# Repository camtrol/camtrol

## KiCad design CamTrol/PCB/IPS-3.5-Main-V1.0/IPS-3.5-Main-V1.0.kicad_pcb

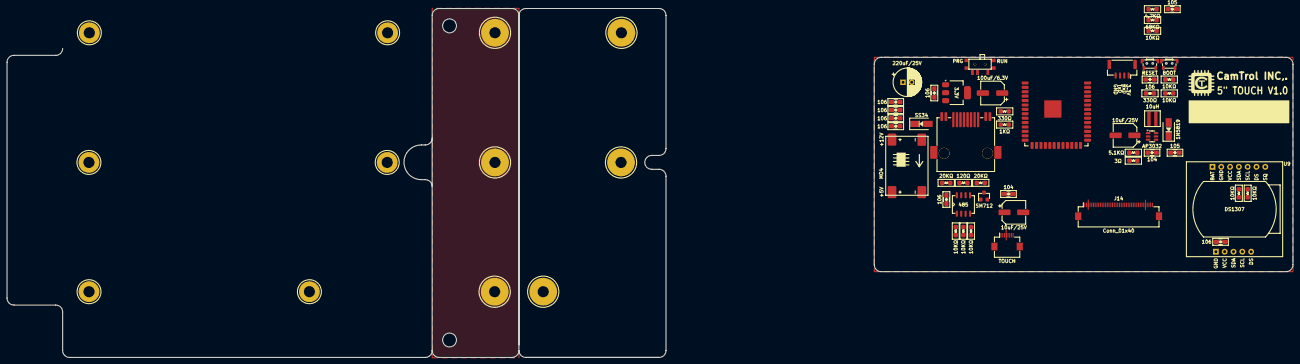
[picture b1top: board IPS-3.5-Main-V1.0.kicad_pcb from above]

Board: 2 copper layers, 370.8 x 100.6 mm, 63 parts (0 on the bottom side), 53 nets.

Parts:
C1, C2, C3, C4, C15, C18, C20, C38: 106; C_0805_HandSoldering
C5, C36: 105; C_0805_HandSoldering
C13, C35: 10uF/25V; CP_Elec_6.3x3
C14, C37: 104; C_0805_HandSoldering
C17: 220uF/25V; CP_Radial_D8.0mm_P2.50mm
C19: 100uF/6.3V; CP_Elec_6.3x5.3
D28: SM712; SOT-23
D33: SS34; D_SMA
D37: 1N5819; D_SMA
H1, H8, H9, H10, H12: MH; MountingHole_3.2mm_M3-support
H2, H3, H4, H5, H6, H7: MH; MountingHole_3.2mm_M3-pcb
He1: MH; MountingHole_3.2mm_M3-support
J1: Conn_01x04_Pin; JST_GH_SM04B-GHS-TB_1x04-1MP_P1.25mm_Horizontal
J6: TOUCH; Hirose_FH12-8S-0.5SH_1x08-1MP_P0.50mm_Horizontal
J8: RJ45_LED; RJ45_LED_SMD
J14: Conn_01x40; Hirose_FH12-40S-0.5SH_1x40-1MP_P0.50mm_Horizontal
L2: 10uH; CD43
MO4: MP1584; TZT-SMD
R1: 4.7KΩ; R_0805_HandSoldering
R2: 68KΩ; R_0805_HandSoldering
R3, R37, R38, R47, R56, R59, R60, R61: 10KΩ; R_0805_HandSoldering
R58, R74: 330Ω; R_0805_HandSoldering
R65: 5.1KΩ; R_0805_HandSoldering
R66: 3Ω; R_0805_HandSoldering
R70, R72: 20KΩ; R_0805_HandSoldering
R71: 120Ω; R_0805_HandSoldering
R73: 1KΩ; R_0805_HandSoldering
SW1: NW3-SK-02
SW2, SW3: SW_Push; MP3-2x4x3.5mm-TACT
U3: 3.3V; SOT-223
U5: ESP32-S3-PCB
U7: AP3032; SOT-23-6
U8: 485; MAX485
U9: DS1307

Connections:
+3V3: C13.1, C14.1, C19.1, C38.1, J6.5, J14.4, R56.1, R59.2, R60.1, R61.1, R74.2, SW1.2 (B), U5.2 (3V3), U9.5 (VCC)
+5V: C15.1, C18.1, C35.1, L2.1, MO4.4 (+5V), R1.2, R37.2, R38.2, R47.2, R72.2, R73.1, U3.3 (VI), U7.6 (V_{IN}), U8.8 (VCC)
+12P: D33.1 (A), J8.1, J8.2
/485-A: D28.1 (A1), J8.6, R71.1, R72.1, U8.6 (A)
/485-B: D28.2 (A2), J8.5, R70.1, R71.2, U8.7 (B)
B3: J14.24, U5.22 (IO_14)
B4: J14.25, U5.31 (IO_38)
B5: J14.26, U5.11 (IO_18)
B6: J14.27, U5.10 (IO_17)
B7: J14.28, U5.18 (IO_10)
BL_EN_1: R3.2, U5.21 (IO_13)
BOOT: R59.1, SW3.2, U5.27 (IO_0)
CTP_IRQ: J6.3, U5.4 (IO_4)
CTP_RST: J6.4, U5.19 (IO_11)
DCLK: J14.30, U5.7 (IO_7)
DE: J14.34, U5.5 (IO_5)
DI: R37.1, U5.8 (IO_15), U8.4 (DI)
DISP: J14.31, R1.1, U7.4 (CTRL)
EN: C20.1, R56.2, R58.1, U5.3 (EN)
ENABLE: R38.1, U5.14 (IO_20), U8.2 (~RE), U8.3 (DE)
G2: J14.15, U5.32 (TCK/IO_39)
G3: J14.16, U5.13 (IO_19)
G4: J14.17, U5.26 (IO_45)
G5: J14.18, U5.25 (IO_48)
G6: J14.19, U5.24 (IO_47)
G7: J14.20, U5.23 (IO_21)
GNDPWR: C1.1, C2.1, C3.1, C4.1, C5.2, C13.2, C14.2, C15.2, C17.2, C18.2, C19.2, C20.2, C35.2, C36.2, C37.2, C38.2, D28.3 (common), H2.1, H3.1, H4.1, H5.1, H6.1, H7.1, J1.4, J1.MP (Pin_5), J6.1, J6.2, J6.8 (Pin_6), J6.MP (Pin_6), J8.3, J8.4, J8.9, J8.11, J8.SH, J14.3, J14.29, J14.36, J14.MP (Pin_50), MO4.1 (GND), MO4.3 (GND), R66.2, R70.2, SW1.4 (C), SW2.1, SW2.MP, SW3.1, SW3.MP, U3.1 (GND), U5.1 (GND), U5.40 (GND), U5.41 (GND), U7.2 (GND), U8.5 (GND), U9.6 (GND)
HSYSNC: J14.32, U5.16 (IO_46)
LCD_RST: J14.35, U5.20 (IO_12)
unnamed: C5.1, R2.1, R3.1
unnamed: C1.2, C2.2, C3.2, C4.2, C17.1, D33.2 (K), MO4.2 (+12V)
unnamed: D37.1 (A), L2.2, U7.1 (SW)
unnamed: H1.1, H8.1, H9.1
unnamed: H10.1, H12.1, He1.1
unnamed: J1.1, SW1.3 (C)
unnamed: J8.10, R74.1
unnamed: J8.12, R73.2
unnamed: R58.2, SW2.2
unnamed: SW1.1 (A), U3.2 (VO)
unnamed: R2.2, R65.1, U7.3 (FB)
R3: J14.8, U5.39 (IO_1)
R4: J14.9, U5.38 (IO_2)
R5: J14.10, U5.35 (TMS/IO_42)
R6: J14.11, U5.34 (TDI/IO_41)
R7: J14.12, U5.33 (TDO/IO_40)
RO: R47.1, U5.9 (IO_16), U8.1 (RO)
RxD0: J1.2, U5.36 (RxD0)
SCL: R60.2, U5.17 (IO_9), U9.3 (SCL)
SDA: R61.2, U5.12 (IO_8), U9.4 (SDA)
TxD0: J1.3, U5.37 (TxD0)
VLED+: C36.1, C37.1, D37.2 (K), J14.2, U7.5 (V_{OUT})
VLED-: J14.1, R65.2, R66.1
VSYSNC: J14.33, U5.15 (IO_3)

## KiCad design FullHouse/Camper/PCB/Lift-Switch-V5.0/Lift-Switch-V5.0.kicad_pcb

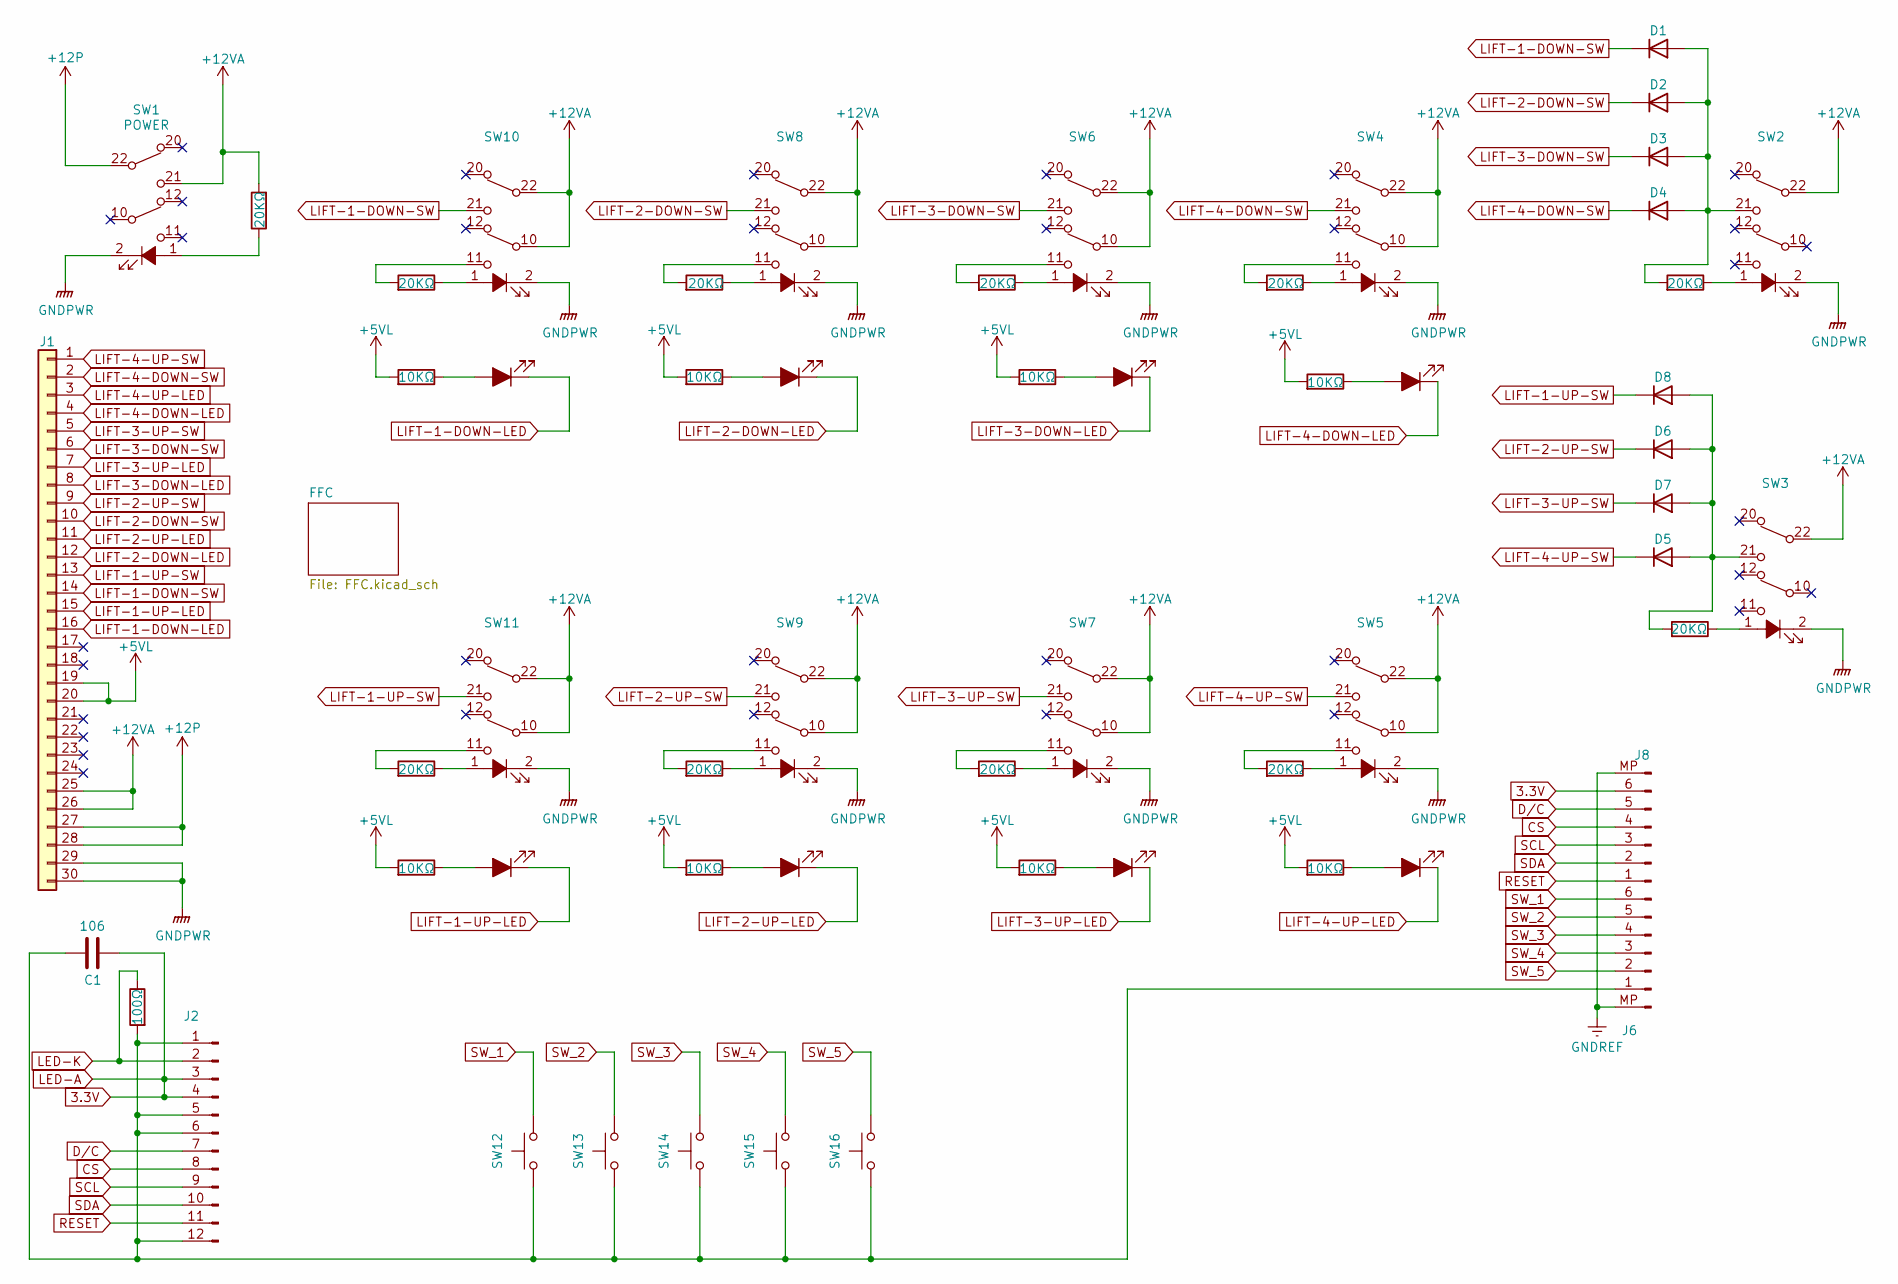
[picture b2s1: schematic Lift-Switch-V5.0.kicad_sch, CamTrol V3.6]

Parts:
C1: 106; C_0805_HandSoldering
D1, D2, D3, D4, D5, D6, D7, D8: type="D" model="1N4148W" lib=""; D_SOD-123
D9, D10, D11, D12, D13, D14, D15, D16: RED LED; LED_D3.0mm_FlatTop
J1: Conn_01x30; IDC-Header_2x15_P2.54mm_Vertical
J2: Conn_01x12_Male; 1.47_IPS
J6, J8: Conn_01x06_Pin; JST_GH_SM06B-GHS-TB_1x06-1MP_P1.25mm_Horizontal
R1, R2, R3, R4, R5, R6, R7, R8, R9, R10, R11: 20KΩ; R_0805_HandSoldering
R12, R13, R14, R15, R16, R17, R18, R19: 10KΩ; R_0805_HandSoldering
R20: 100Ω; R_0805_HandSoldering
SW1, SW2, SW3, SW4, SW5, SW6, SW7, SW8, SW10, SW11: POWER; P2-L
SW9: E; P2-L
SW12, SW13, SW14, SW15, SW16: SW_Push; TS-3404

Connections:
3.3V: C1.2, J2.3, J2.4, J8.6
+5VL: J1.19, J1.20, R12.2, R13.2, R14.2, R15.2, R16.2, R17.2, R18.2, R19.2
+12P: J1.27, J1.28, SW1.22 (COM)
+12VA: J1.25, J1.26, R1.2, SW1.21 (NO), SW2.22 (COM), SW3.22 (COM), SW4.10 (COM), SW4.22 (COM), SW5.10 (COM), SW5.22 (COM), SW6.10 (COM), SW6.22 (COM), SW7.10 (COM), SW7.22 (COM), SW8.10 (COM), SW8.22 (COM), SW9.10 (COM), SW9.22 (COM), SW10.10 (COM), SW10.22 (COM), SW11.10 (COM), SW11.22 (COM)
CS: J2.8, J8.4
D/C: J2.7, J8.5
GNDPWR: J1.29, J1.30, SW1.2 (K), SW2.2 (K), SW3.2 (K), SW4.2 (K), SW5.2 (K), SW6.2 (K), SW7.2 (K), SW8.2 (K), SW9.2 (K), SW10.2 (K), SW11.2 (K)
GNDREF: J6.MP (Pin_1), J8.MP (Pin_7)
LED-K: J2.2, R20.1
LIFT-1-DOWN-LED: D9.1 (K), J1.16
LIFT-1-DOWN-SW: D1.2 (K), J1.14, SW10.21 (NO)
LIFT-1-UP-LED: D10.1 (K), J1.15
LIFT-1-UP-SW: D8.2 (K), J1.13, SW11.21 (NO)
LIFT-2-DOWN-LED: D11.1 (K), J1.12
LIFT-2-DOWN-SW: D2.2 (K), J1.10, SW8.21 (NO)
LIFT-2-UP-LED: D12.1 (K), J1.11
LIFT-2-UP-SW: D6.2 (K), J1.9, SW9.21 (NO)
LIFT-3-DOWN-LED: D13.1 (K), J1.8
LIFT-3-DOWN-SW: D3.2 (K), J1.6, SW6.21 (NO)
LIFT-3-UP-LED: D14.1 (K), J1.7
LIFT-3-UP-SW: D7.2 (K), J1.5, SW7.21 (NO)
LIFT-4-DOWN-LED: D15.1 (K), J1.4
LIFT-4-DOWN-SW: D4.2 (K), J1.2, SW4.21 (NO)
LIFT-4-UP-LED: D16.1 (K), J1.3
LIFT-4-UP-SW: D5.2 (K), J1.1, SW5.21 (NO)
unnamed: D1.1 (A), D2.1 (A), D3.1 (A), D4.1 (A), R2.2, SW2.21 (NO)
unnamed: D5.1 (A), D6.1 (A), D7.1 (A), D8.1 (A), R3.2, SW3.21 (NO)
unnamed: D9.2 (A), R12.1
unnamed: D10.2 (A), R13.1
unnamed: D11.2 (A), R14.1
unnamed: D12.2 (A), R15.1
unnamed: D13.2 (A), R16.1
unnamed: D14.2 (A), R17.1
unnamed: D15.2 (A), R18.1
unnamed: D16.2 (A), R19.1
unnamed: C1.1, J2.1, J2.5, J2.6, J2.12, J6.1 (Pin_2), R20.2, SW12.1, SW13.1, SW14.1, SW15.1, SW16.1
unnamed: R4.2, SW4.11 (NO)
unnamed: R5.2, SW5.11 (NO)
unnamed: R6.2, SW6.11 (NO)
unnamed: R7.2, SW7.11 (NO)
unnamed: R8.2, SW8.11 (NO)
unnamed: R9.2, SW9.11 (NO)
unnamed: R10.2, SW10.11 (NO)
unnamed: R11.2, SW11.11 (NO)
unnamed: R1.1, SW1.1 (A)
unnamed: R2.1, SW2.1 (A)
unnamed: R3.1, SW3.1 (A)
unnamed: R4.1, SW4.1 (A)
unnamed: R5.1, SW5.1 (A)
unnamed: R6.1, SW6.1 (A)
unnamed: R7.1, SW7.1 (A)
unnamed: R8.1, SW8.1 (A)
unnamed: R9.1, SW9.1 (A)
unnamed: R10.1, SW10.1 (A)
unnamed: R11.1, SW11.1 (A)
RESET: J2.11, J8.1
SCL: J2.9, J8.3
SDA: J2.10, J8.2
SW_1: J6.6 (Pin_7), SW12.2
SW_2: J6.5 (Pin_6), SW13.2
SW_3: J6.4 (Pin_5), SW14.2
SW_4: J6.3 (Pin_4), SW15.2
SW_5: J6.2 (Pin_3), SW16.2

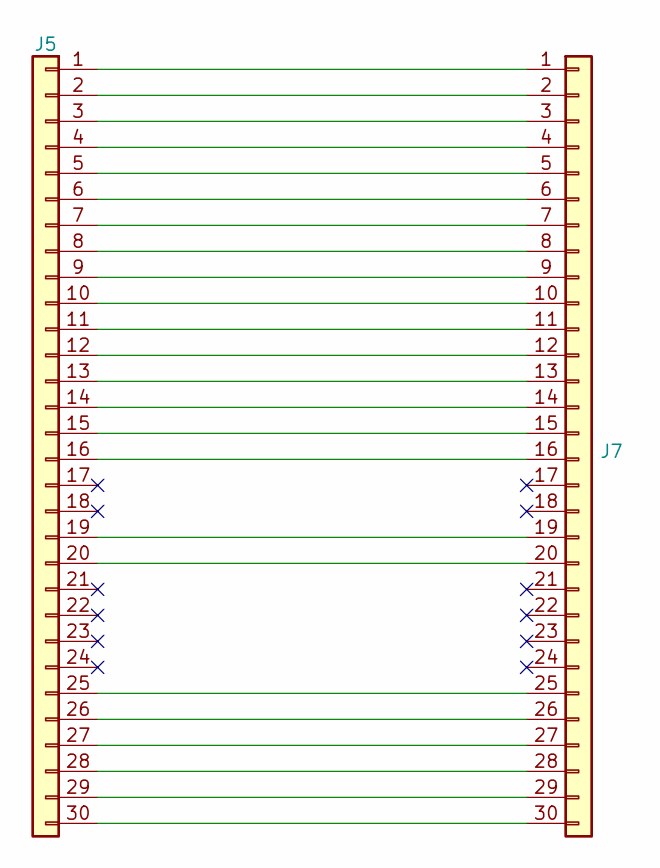
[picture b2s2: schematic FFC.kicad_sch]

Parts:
J5: Conn_01x30; IDC-Header_2x15_P2.54mm_Vertical
J7: Conn_01x30; Hirose_FH12-30S-0.5SH_1x30-1MP_P0.50mm_Horizontal

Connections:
unnamed: J5.1, J7.1
unnamed: J5.2, J7.2
unnamed: J5.3, J7.3
unnamed: J5.4, J7.4
unnamed: J5.5, J7.5
unnamed: J5.6, J7.6
unnamed: J5.7, J7.7
unnamed: J5.8, J7.8
unnamed: J5.9, J7.9
unnamed: J5.10, J7.10
unnamed: J5.11, J7.11
unnamed: J5.12, J7.12
unnamed: J5.13, J7.13
unnamed: J5.14, J7.14
unnamed: J5.15, J7.15
unnamed: J5.16, J7.16
unnamed: J5.19, J7.19
unnamed: J5.20, J7.20
unnamed: J5.25, J7.25
unnamed: J5.26, J7.26
unnamed: J5.27, J7.27
unnamed: J5.28, J7.28
unnamed: J5.29, J7.29
unnamed: J5.30, J7.30

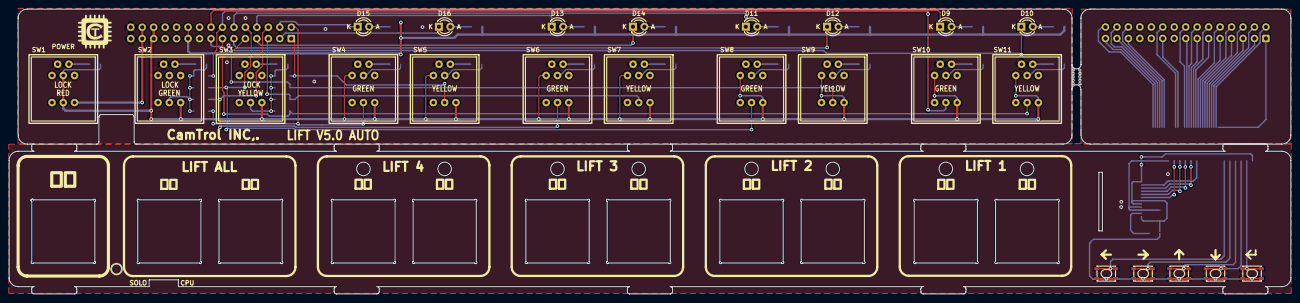
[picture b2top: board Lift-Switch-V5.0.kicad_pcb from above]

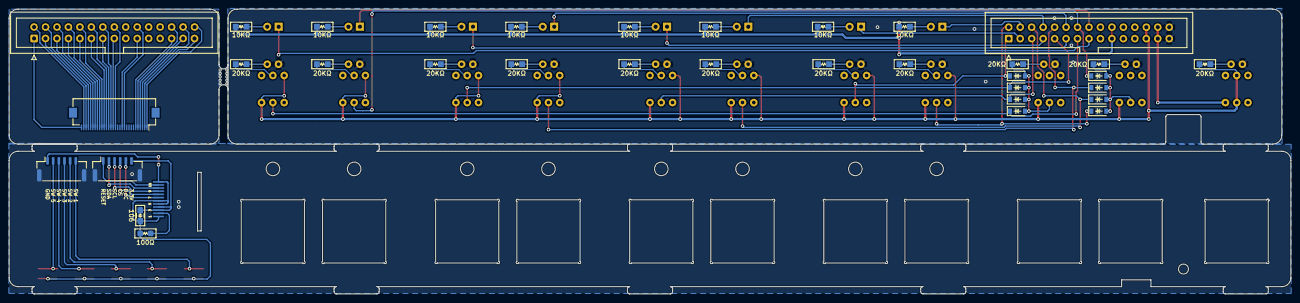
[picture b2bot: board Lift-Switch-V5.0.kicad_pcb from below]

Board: 2 copper layers, 284.0 x 63.1 mm, 60 parts (35 on the bottom side), 87 nets.

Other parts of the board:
mouse-bite-2mm-slot: VAL**; mouse-bite-3mm-slot

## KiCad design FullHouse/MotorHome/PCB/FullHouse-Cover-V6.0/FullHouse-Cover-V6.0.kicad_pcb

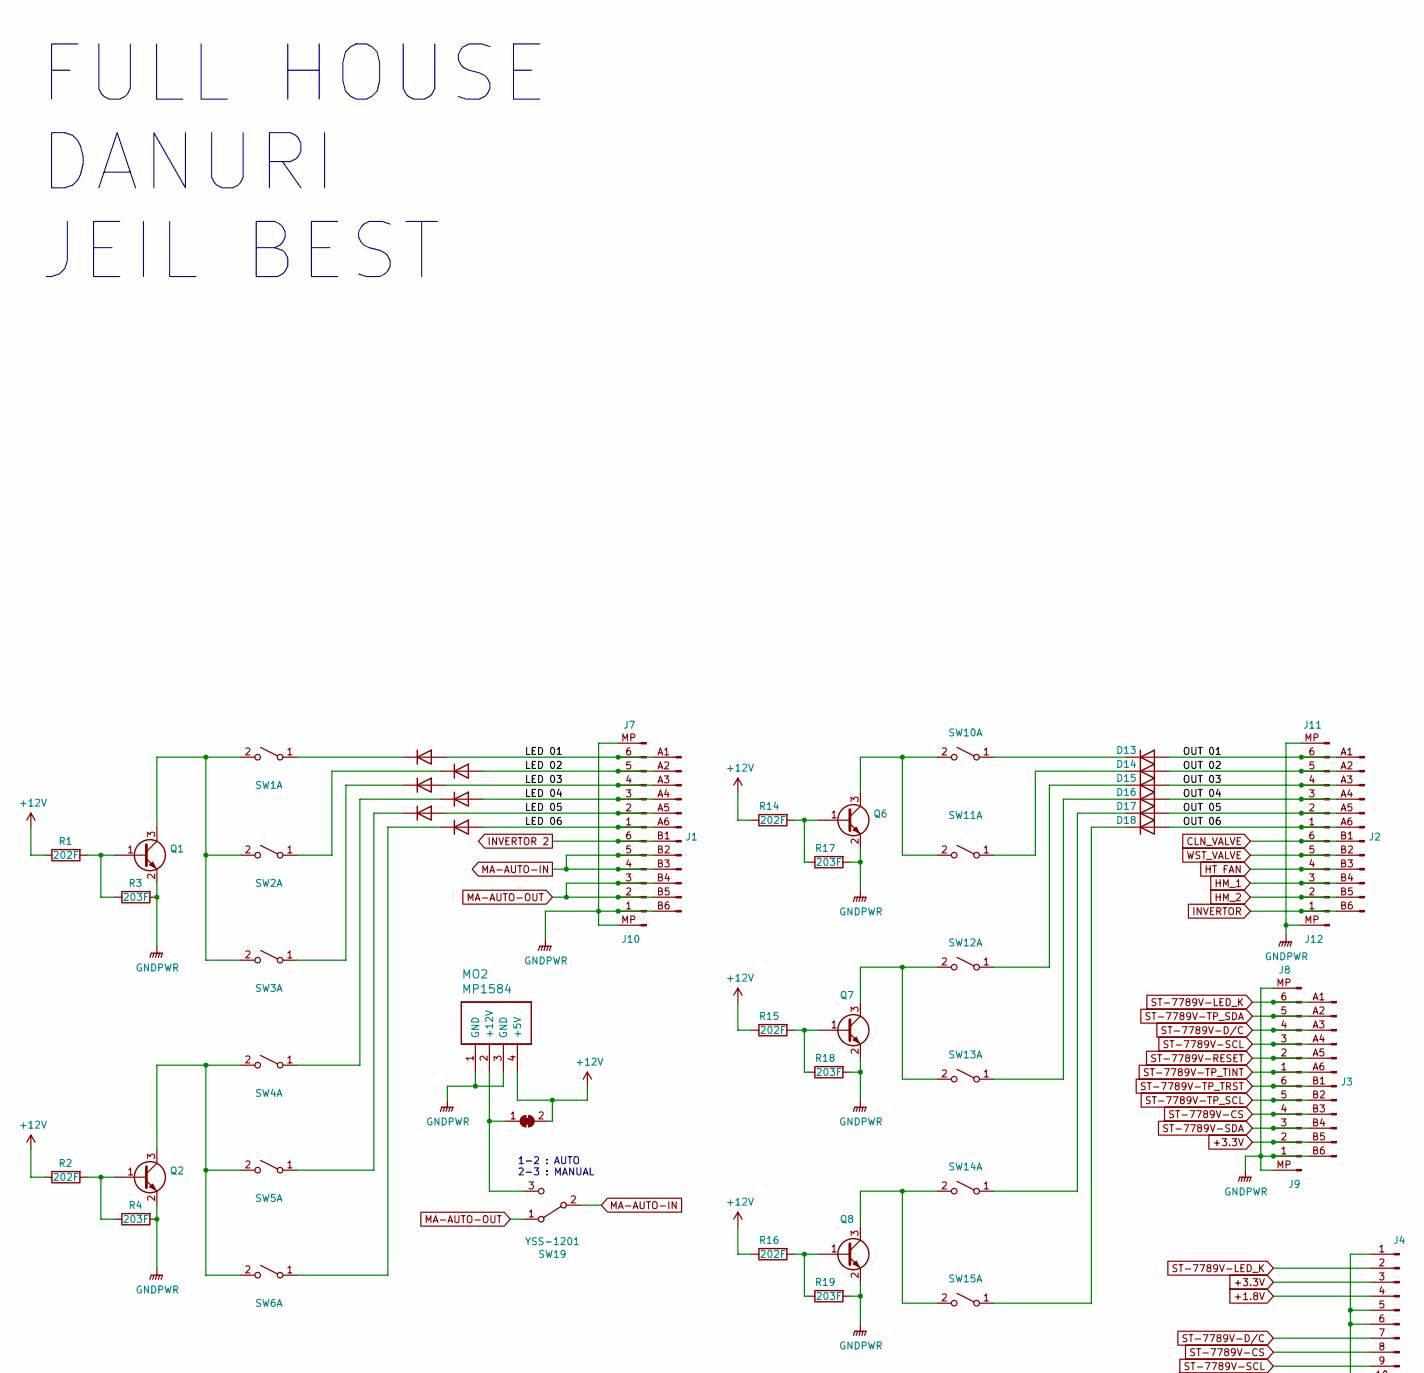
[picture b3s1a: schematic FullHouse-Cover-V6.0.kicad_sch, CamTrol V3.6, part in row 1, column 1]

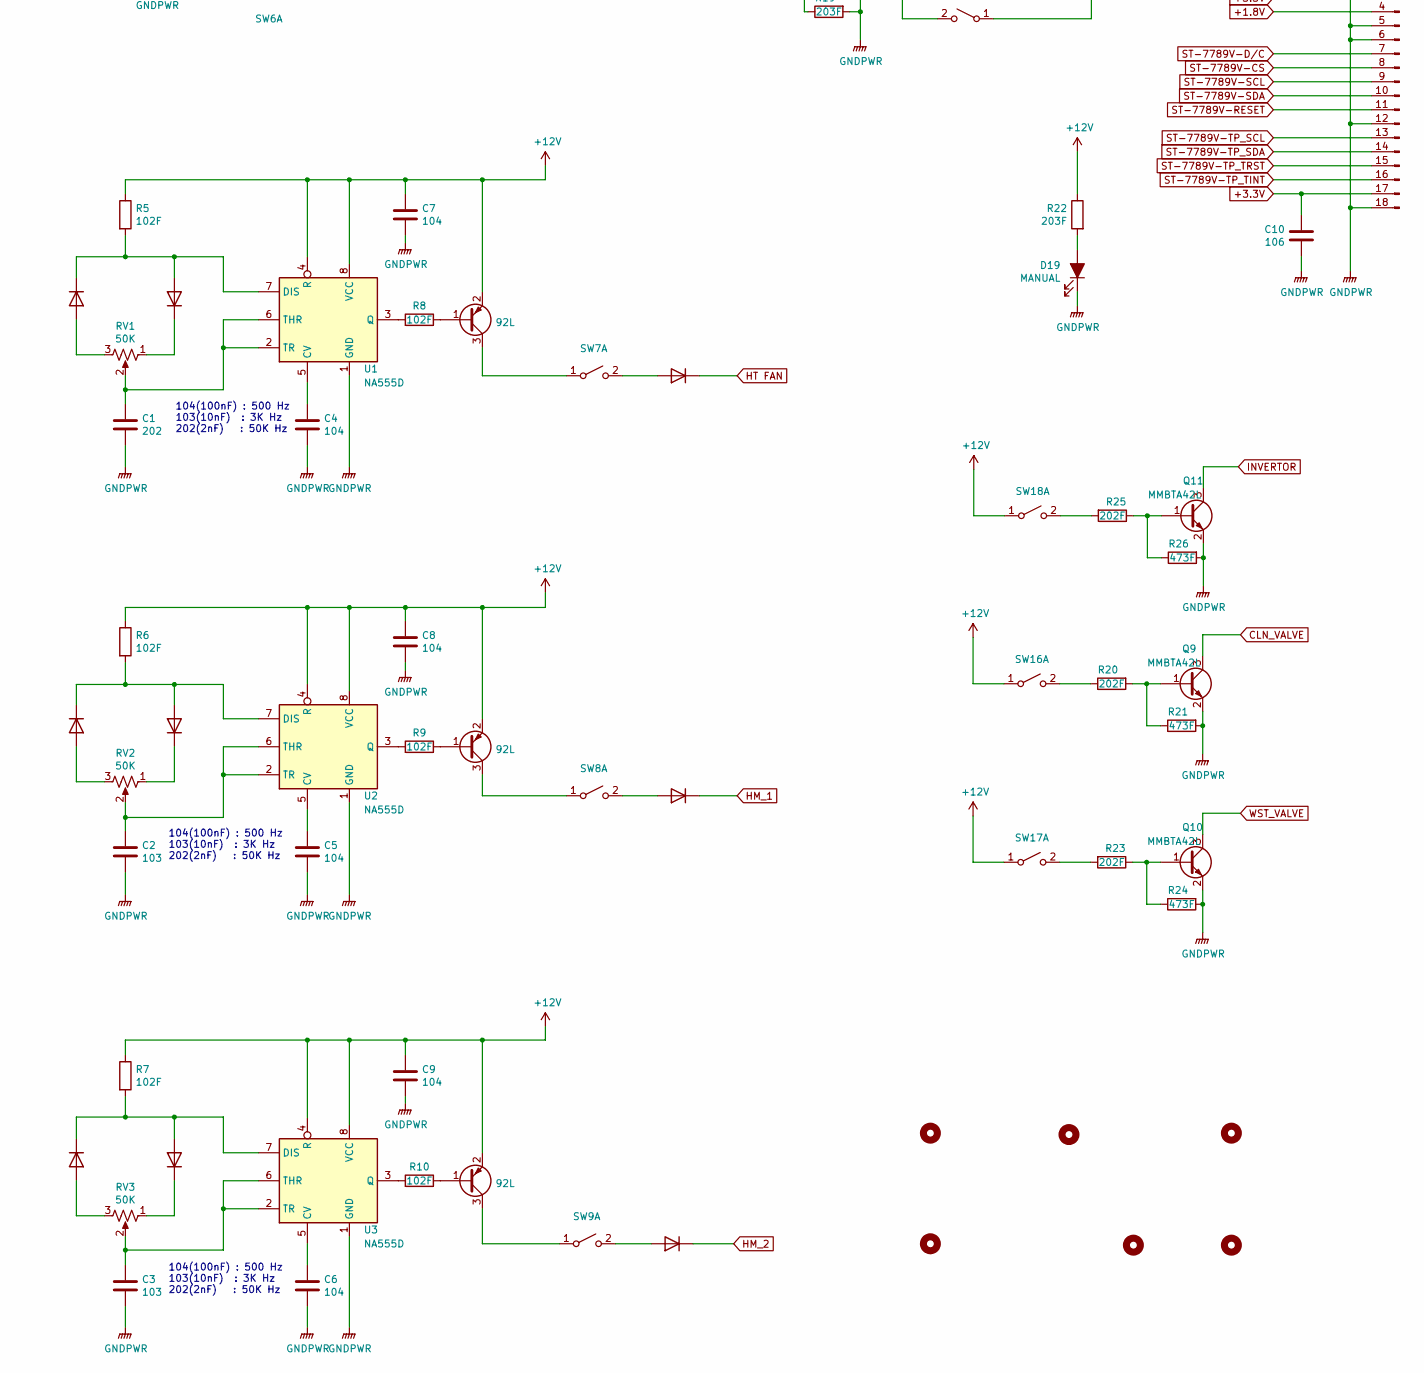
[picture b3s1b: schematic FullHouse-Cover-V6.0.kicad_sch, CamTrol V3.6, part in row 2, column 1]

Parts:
C1: 202; C_0805_HandSoldering
C2, C3: 103; C_0805_HandSoldering
C4, C5, C6, C7, C8, C9: 104; C_0805_HandSoldering
C10: 106; C_0805_HandSoldering
D1, D2, D3, D4, D5, D6, D7, D8, D9, D10, D11, D12, D13, D14, D15, D16, D17, D18, D20, D21, D22: type="D" model="1N4148W" lib=""; D_SOD-123
D19: MANUAL; LED_0805
H1, H2, H4, H5, H6, H7: MH; MountingHole_3.2mm_M3-pcb
J1, J2, J3: Conn_01x12_Male; SMD_CONN_1x12_P1.270mm
J4: Conn_01x12_Male; Hirose_FH12-18S-0.5SH_1x18-1MP_P0.50mm_Horizontal_ST7789V3-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
J7, J8, J9, J10, J11, J12: Conn_01x06_Pin; JST_GH_SM06B-GHS-TB_1x06-1MP_P1.25mm_Horizontal
JP1: SolderJumper; SolderJumper-2_P1.3mm_Bridged_RoundedPad1.0x1.5mm
MO2: MP1584; TZT-SMD
Q1, Q2, Q6, Q7, Q8, Q9, Q10, Q11: MMBTA42L; SOT-23
Q3, Q4, Q5: 92L; SOT-23
R1, R2, R14, R15, R16, R20, R23, R25: 202F; R_0805_HandSoldering
R3, R4, R17, R18, R19, R22: 203F; R_0805_HandSoldering
R5, R6, R7, R8, R9, R10: 102F; R_0805_HandSoldering
R21, R24, R26: 473F; R_0805_HandSoldering
RV1, RV2, RV3: 50K; RV09H
SW1, SW2, SW3, SW4, SW5, SW6, SW7, SW8, SW9, SW10, SW11, SW12, SW13, SW14, SW15, SW16, SW17, SW18: YSS-1201; 8.5x8.5_Push_Lock
SW19: YSS-1201
U1, U2, U3: NA555D; NE555

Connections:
+1.8V: J4.4
+3.3V: C10.2, J3.B5 (Pin_11), J4.3, J4.17, J9.2 (Pin_5)
+12V: C7.2, C8.2, C9.2, JP1.2 (B), MO2.4 (+5V), Q3.2 (E), Q4.2 (E), Q5.2 (E), R1.1, R2.1, R5.1, R6.1, R7.1, R14.1, R15.1, R16.1, R22.1, SW16.1 (A), SW17.1 (A), SW18.1 (A), U1.4 (R), U1.8 (VCC), U2.4 (R), U2.8 (VCC), U3.4 (R), U3.8 (VCC)
/LED 01: D7.1 (A), J1.A1 (Pin_1), J7.6 (Pin_2)
/LED 02: D8.1 (A), J1.A2 (Pin_2), J7.5 (Pin_3)
/LED 03: D9.1 (A), J1.A3 (Pin_3), J7.4
/LED 04: D10.1 (A), J1.A4 (Pin_4), J7.3 (Pin_5)
/LED 05: D11.1 (A), J1.A5 (Pin_5), J7.2 (Pin_6)
/LED 06: D12.1 (A), J1.A6 (Pin_6), J7.1 (Pin_7)
/OUT 01: D13.1 (A), J2.A1 (Pin_1), J11.6 (Pin_2)
/OUT 02: D14.1 (A), J2.A2 (Pin_2), J11.5 (Pin_3)
/OUT 03: D15.1 (A), J2.A3 (Pin_3), J11.4
/OUT 04: D16.1 (A), J2.A4 (Pin_4), J11.3 (Pin_5)
/OUT 05: D17.1 (A), J2.A5 (Pin_5), J11.2 (Pin_6)
/OUT 06: D18.1 (A), J2.A6 (Pin_6), J11.1 (Pin_7)
CLN_VALVE: J2.B1 (Pin_7), J12.6 (Pin_1), Q9.3 (C)
GNDPWR: C1.1, C2.1, C3.1, C4.1, C5.1, C6.1, C7.1, C8.1, C9.1, C10.1, D19.1 (K), J1.B6 (Pin_12), J3.B6 (Pin_12), J4.1, J4.5, J4.6, J4.12, J4.18, J7.MP (Pin_1), J8.MP (Pin_1), J9.1 (Pin_6), J9.MP (Pin_7), J10.1 (Pin_6), J10.MP (Pin_7), J11.MP (Pin_1), J12.MP (Pin_7), MO2.1 (GND), MO2.3 (GND), Q1.2 (E), Q2.2 (E), Q6.2 (E), Q7.2 (E), Q8.2 (E), Q9.2 (E), Q10.2 (E), Q11.2 (E), R3.2, R4.2, R17.2, R18.2, R19.2, R21.2, R24.2, R26.2, U1.1 (GND), U2.1 (GND), U3.1 (GND)
HM_1: D20.2 (K), J2.B4 (Pin_10), J12.3 (Pin_4)
HM_2: D22.2 (K), J2.B5 (Pin_11), J12.2 (Pin_5)
HT FAN: D21.2 (K), J2.B3 (Pin_9), J12.4 (Pin_3)
INVERTOR: J2.B6 (Pin_12), J12.1 (Pin_6), Q11.3 (C)
INVERTOR 2: J1.B1 (Pin_7), J10.6 (Pin_1)
MA-AUTO-IN: J1.B2 (Pin_8), J1.B3 (Pin_9), J10.4 (Pin_3), J10.5 (Pin_2), SW19.2 (B)
MA-AUTO-OUT: J1.B4 (Pin_10), J1.B5 (Pin_11), J10.2 (Pin_5), J10.3 (Pin_4), SW19.1 (A)
unnamed: D1.1 (A), RV1.3
unnamed: D1.2 (K), D4.1 (A), R5.2, U1.7 (DIS)
unnamed: D2.1 (A), RV2.3
unnamed: D2.2 (K), D5.1 (A), R6.2, U2.7 (DIS)
unnamed: D3.1 (A), RV3.3
unnamed: D3.2 (K), D6.1 (A), R7.2, U3.7 (DIS)
unnamed: D4.2 (K), RV1.1
unnamed: D5.2 (K), RV2.1
unnamed: D6.2 (K), RV3.1
unnamed: D7.2 (K), SW1.1 (A)
unnamed: D8.2 (K), SW2.1 (A)
unnamed: D9.2 (K), SW3.1 (A)
unnamed: D10.2 (K), SW4.1 (A)
unnamed: D11.2 (K), SW5.1 (A)
unnamed: D12.2 (K), SW6.1 (A)
unnamed: D13.2 (K), SW10.1 (A)
unnamed: D14.2 (K), SW11.1 (A)
unnamed: D15.2 (K), SW12.1 (A)
unnamed: D16.2 (K), SW13.1 (A)
unnamed: D17.2 (K), SW14.1 (A)
unnamed: D18.2 (K), SW15.1 (A)
unnamed: D19.2 (A), R22.2
unnamed: D20.1 (A), SW8.2 (B)
unnamed: D21.1 (A), SW7.2 (B)
unnamed: D22.1 (A), SW9.2 (B)
unnamed: JP1.1 (A), MO2.2 (+12V), SW19.3 (C)
unnamed: Q1.1 (B), R1.2, R3.1
unnamed: Q1.3 (C), SW1.2 (B), SW2.2 (B), SW3.2 (B)
unnamed: Q2.1 (B), R2.2, R4.1
unnamed: Q2.3 (C), SW4.2 (B), SW5.2 (B), SW6.2 (B)
unnamed: Q3.1 (B), R8.1
unnamed: Q3.3 (C), SW7.1 (A)
unnamed: Q4.1 (B), R9.1
unnamed: Q4.3 (C), SW8.1 (A)
unnamed: Q5.1 (B), R10.1
unnamed: Q5.3 (C), SW9.1 (A)
unnamed: Q6.1 (B), R14.2, R17.1
unnamed: Q6.3 (C), SW10.2 (B), SW11.2 (B)
unnamed: Q7.1 (B), R15.2, R18.1
unnamed: Q7.3 (C), SW12.2 (B), SW13.2 (B)
unnamed: Q8.1 (B), R16.2, R19.1
unnamed: Q8.3 (C), SW14.2 (B), SW15.2 (B)
unnamed: Q9.1 (B), R20.2, R21.1
unnamed: Q10.1 (B), R23.1, R24.1
unnamed: Q11.1 (B), R25.1, R26.1
unnamed: R20.1, SW16.2 (B)
unnamed: R23.2, SW17.2 (B)
unnamed: R25.2, SW18.2 (B)
unnamed: C4.2, U1.5 (CV)
unnamed: R8.2, U1.3 (Q)
unnamed: C1.2, RV1.2, U1.2 (TR), U1.6 (THR)
unnamed: C5.2, U2.5 (CV)
unnamed: R9.2, U2.3 (Q)
unnamed: C2.2, RV2.2, U2.2 (TR), U2.6 (THR)
unnamed: C6.2, U3.5 (CV)
unnamed: R10.2, U3.3 (Q)
unnamed: C3.2, RV3.2, U3.2 (TR), U3.6 (THR)
ST-7789V-CS: J3.B3 (Pin_9), J4.8, J9.4 (Pin_3)
ST-7789V-D/C: J3.A3 (Pin_3), J4.7, J8.4
ST-7789V-LED_K: J3.A1 (Pin_1), J4.2, J8.6 (Pin_2)
ST-7789V-RESET: J3.A5 (Pin_5), J4.11, J8.2 (Pin_6)
ST-7789V-SCL: J3.A4 (Pin_4), J4.9, J8.3 (Pin_5)
ST-7789V-SDA: J3.B4 (Pin_10), J4.10, J9.3 (Pin_4)
ST-7789V-TP_SCL: J3.B2 (Pin_8), J4.13, J9.5 (Pin_2)
ST-7789V-TP_SDA: J3.A2 (Pin_2), J4.14, J8.5 (Pin_3)
ST-7789V-TP_TINT: J3.A6 (Pin_6), J4.16, J8.1 (Pin_7)
ST-7789V-TP_TRST: J3.B1 (Pin_7), J4.15, J9.6 (Pin_1)
WST_VALVE: J2.B2 (Pin_8), J12.5 (Pin_2), Q10.3 (C)

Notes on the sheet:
1-2 : AUTO 2-3 : MANUAL
104(100nF) : 500 Hz 103(10nF) : 3K Hz 202(2nF) : 50K Hz
FULL HOUSE DANURI JEIL BEST

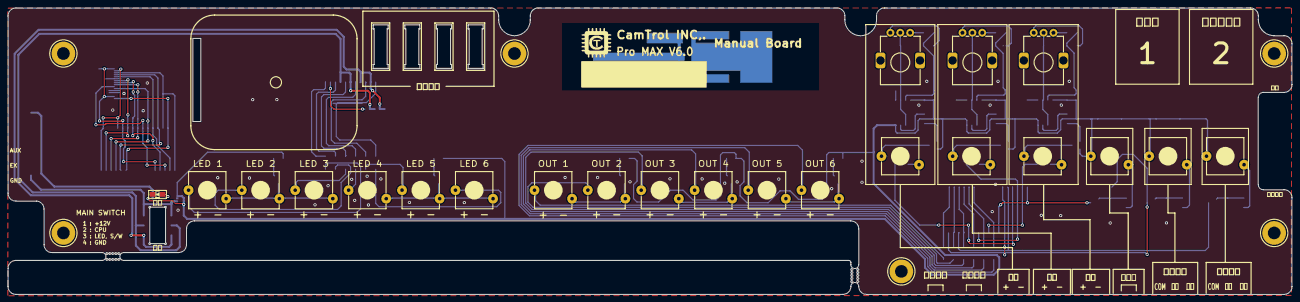
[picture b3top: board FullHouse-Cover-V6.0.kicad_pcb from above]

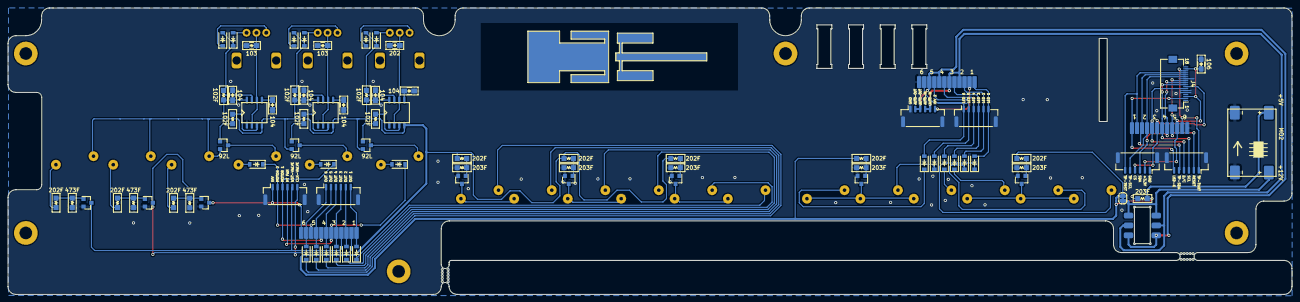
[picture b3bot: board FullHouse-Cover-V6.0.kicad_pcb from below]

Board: 2 copper layers, 324.5 x 72.4 mm, 117 parts (81 on the bottom side), 91 nets.

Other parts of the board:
A1: IPX-ANTENA
SF1, SF2, SF3, SF4: FUSE; FUSE-Holder-mini
U4: 1.3 OLED; ST7789V
mouse-bite-2mm-slot, mouse-bite-2mm-slot#2: VAL**; mouse-bite-3mm-slot
